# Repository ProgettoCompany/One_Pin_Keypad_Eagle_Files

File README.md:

# Progetto One Pin Keypad Eagle Files
Design files for the One Pin Keypad, a device that simplifies the use of 16 button matrix keypads.
## Documentation:
* [Tindie Product Page](https://www.tindie.com/products/Progetto/one-pin-keypad/)
* [eBay Product Page](http://rover.ebay.com/rover/1/706-53473-19255-0/1?icep_ff3=2&pub=5575378759&campid=5338273189&customid=&icep_item=283391631793&ipn=psmain&icep_vectorid=229529&kwid=902099&mtid=824&kw=lg&toolid=11111)
* [Design Spark Marketplace Product Page](https://www.designsparkmarketplace.com/en/listings/645-one-pin-keypad)
* [Instructables Raspberry Pi tutorial](https://www.instructables.com/id/One-Pin-Keypad-Raspberry-Pi-Usage-Guide/)
* [Instructables Arduino tutorial](https://www.instructables.com/id/Meet-One-Pin-Keypad)
* [Python Package](https://github.com/ProgettoCompany/Progetto_One_Pin_Keypad_Python_Package)
* [Arduino Library](https://github.com/ProgettoCompany/One_Pin_Keypad_Arduino_Library)
## License Information:
This product is open source, the **hardware** is licensed under the [Creative Commons Attribution-ShareAlike 4.0 International License](http://creativecommons.org/licenses/by-sa/4.0/).

Distributed as-is; no warranty is given.
## Contact:
Email us at progettocompany@gmail.com if you have any questions or concerns.

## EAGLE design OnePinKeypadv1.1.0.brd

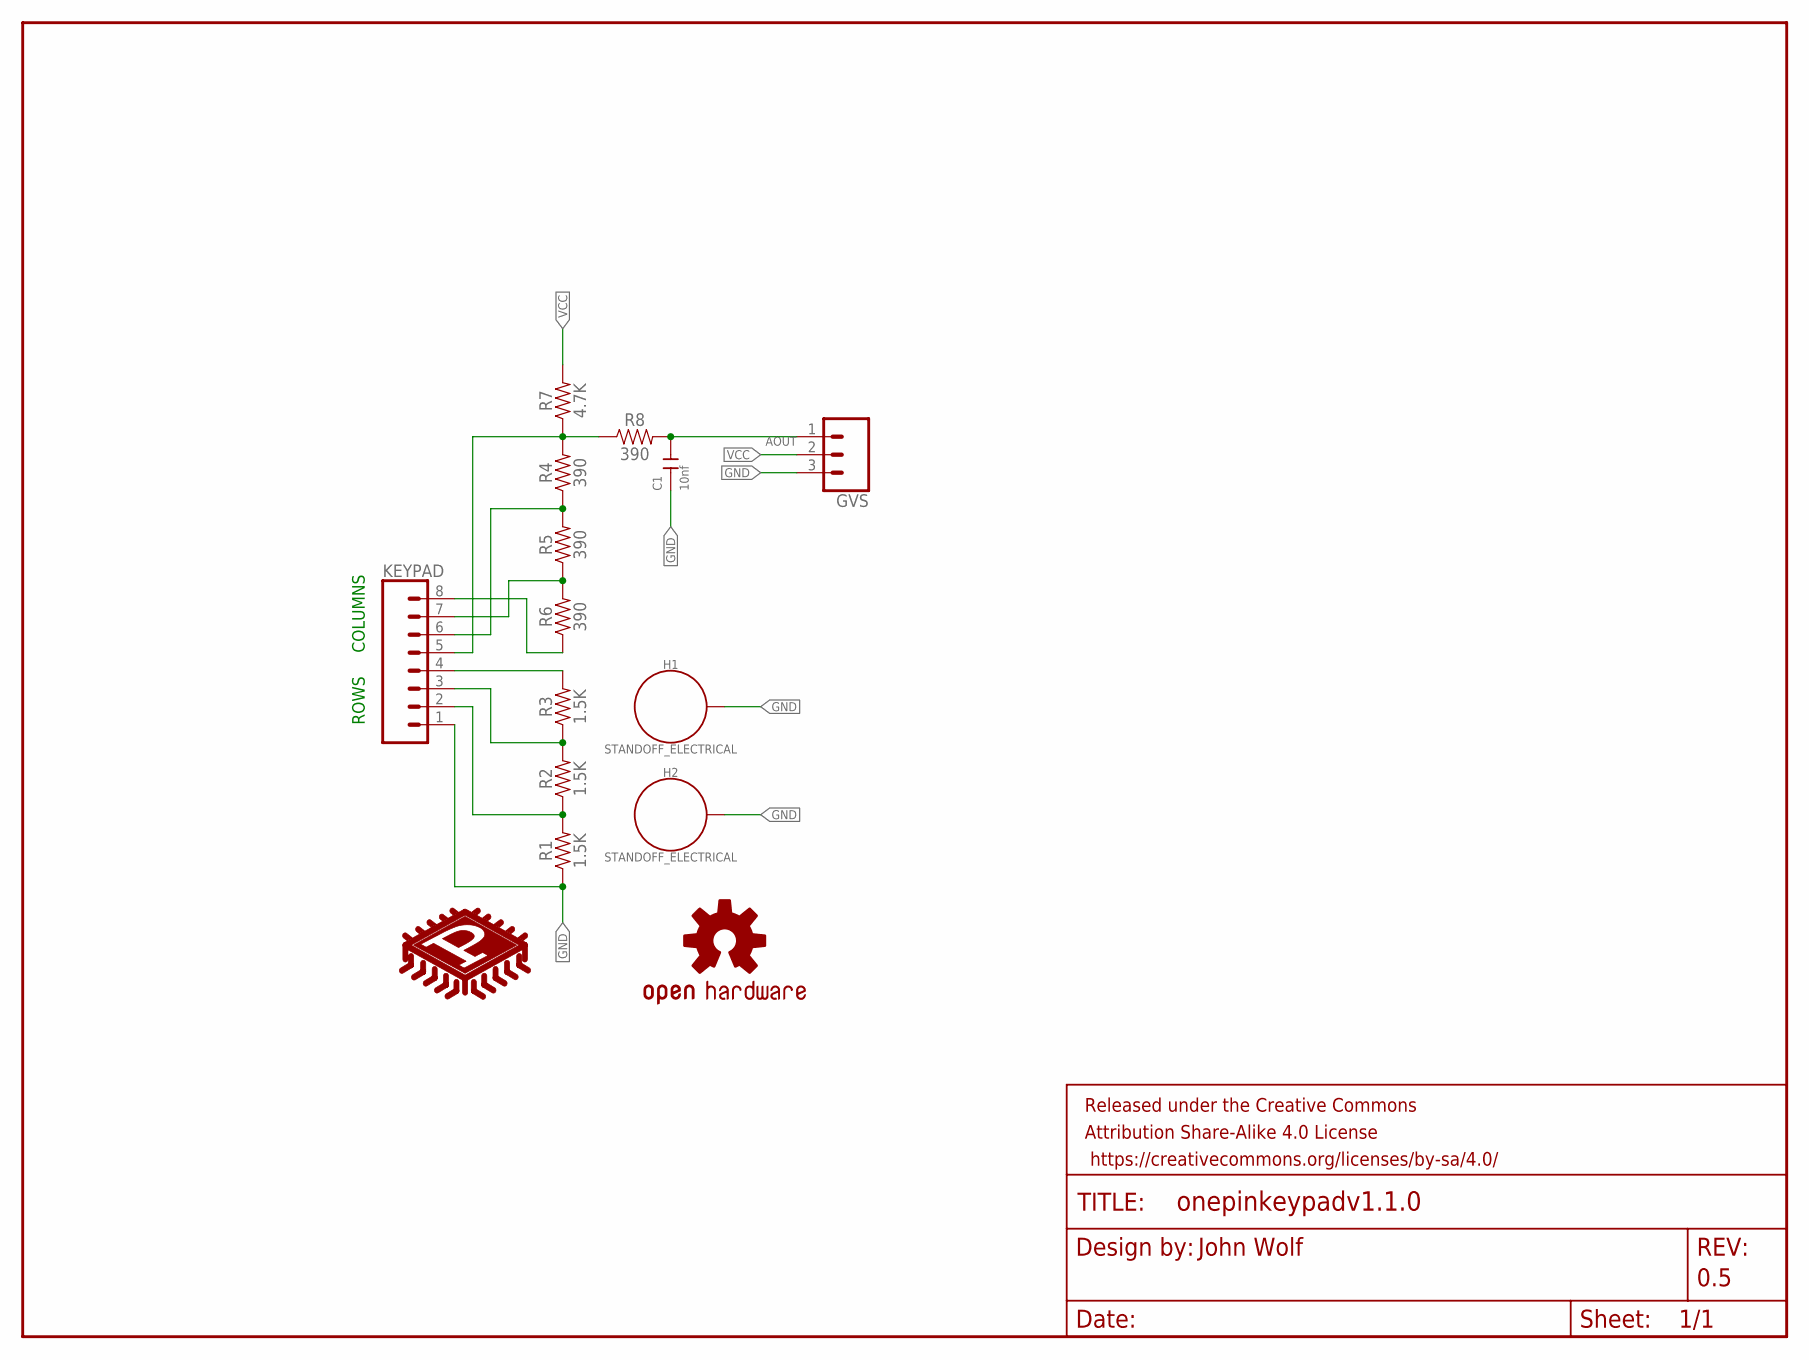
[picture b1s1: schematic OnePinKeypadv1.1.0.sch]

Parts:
C1: 10nf; C0805
FRAME1: FRAME-LETTER; CREATIVE_COMMONS
GVS: CONN_03; 1X03
H1, H2: STANDOFF_ELECTRICAL; STANDOFF-ELECTRICAL
KEYPAD: CONN_08"; 1X08
LOGO1: OSHW-LOGOS; OSHW-LOGO-S
R1, R2, R3: 1.5K; 0805
R4, R5, R6, R8: 390; 0805
R7: 4.7K; 0805
U$2: LOGO_V1

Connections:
AOUT: C1.2, GVS.1, R8.2
COL1: KEYPAD.5, R4.2, R7.1, R8.1
COL2: KEYPAD.6, R4.1, R5.2
COL3: KEYPAD.7, R5.1, R6.2
COL4: KEYPAD.8, R6.1
GND: C1.1, GVS.3, H1.P1, H2.P1, KEYPAD.1, R1.1
ROW2: KEYPAD.2, R1.2, R2.1
ROW3: KEYPAD.3, R2.2, R3.1
ROW4: KEYPAD.4, R3.2
VCC: GVS.2, R7.2

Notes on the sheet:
ROWS
COLUMNS
0.5
John Wolf

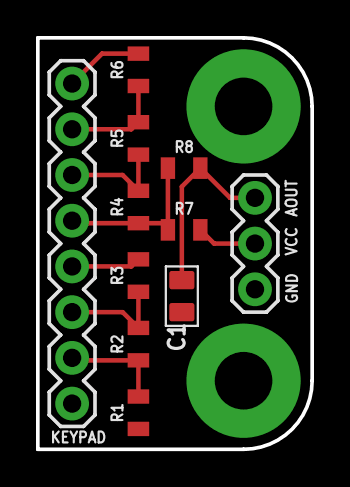
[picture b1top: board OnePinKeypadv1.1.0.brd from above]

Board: 2 copper layers, 15.2 x 22.9 mm, 16 parts (1 on the bottom side), 10 nets.

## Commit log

2018-10-28 Updated Product URL

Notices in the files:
parts and their libraries:
SparkFun-Connectors: Licensing: Creative Commons ShareAlike 4.0 International - https://creativecommons.org/licenses/by-sa/4.0
SparkFun-Aesthetics: Released under the Creative Commons Attribution Share-Alike 4.0 License
SparkFun-Aesthetics: https://creativecommons.org/licenses/by-sa/4.0
